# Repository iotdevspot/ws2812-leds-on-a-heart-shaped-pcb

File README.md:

# ws2812-leds-on-a-heart-shaped-pcb

### About the project
This is a WS2812 LED driver circuit with an ATTiny85 MCU. PCB and the LEDs are aligned to create a heart shape because it's a gift.  Unfortunately, I'm quite sort of time so the code is very basic and it has been created from the examples found on Adafruit's website. In the future I'll upload a newer version. This version is only capable for 4 basic effects witch can be selected with the left function button.

### Contents
* Gerber files (the version that I've sent to the fab house)
* Updated board layout and schematics
* 3D model can be found on my fusion360 gallery
* Code (Arduino sketch and hex)
* Datasheet
* Images of the result

### The following steps are required to deploy the provided .hex, or the Arduino sketch:
* Here is how to program ATTiny MCUs in Arduino IDE: [link](http://highlowtech.org/?p=1695)
* I've used external 16 MHz oscillator (AVR fuse settings needed + hex is compiled this way too) so it might be required but I assume it works on internal clock well too but code should be recompiled
* Code is based on Adafruit's [Neopixel libary and their example projects](https://learn.adafruit.com/adafruit-arduino-lesson-16-stepper-motors/breadboard-layout) so Adafruit's libary might be needed if you want to deploy it from the IDE.
* Finnaly the hex should be uploaded. You can do this by using IDE-s "Upload using programmer" option or .hex file can be uploaded throuh AVR Dude too. It's basically your choice...

### ToDo

* 3D printed mounting for the two mounting holes
* Replace the full bascic code

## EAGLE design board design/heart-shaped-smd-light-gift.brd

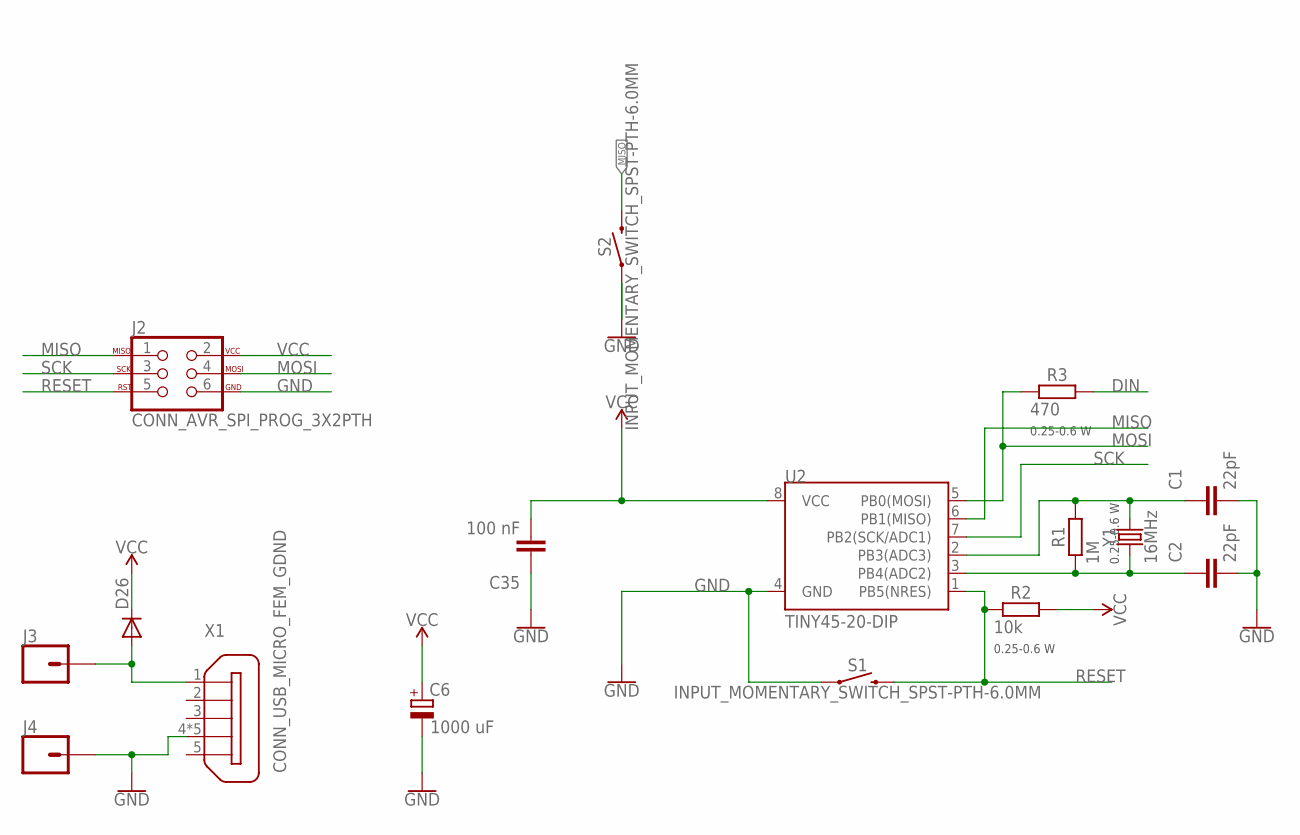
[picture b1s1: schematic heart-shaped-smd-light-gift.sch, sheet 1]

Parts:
C1, C2: 22pF; C1206I-C3216M
C6: 1000 uF; 153CLV-1010
C35: 100 nF; C1206I-C3216M
D26: DIODED-7.5; D-7.5
J2: CONN_AVR_SPI_PROG_3X2PTH; 2X3_S
J3, J4: CONN_01SNAP-MALE; SNAP-MALE
R1: 1M; 0207/7
R2: 10k; 0207/7
R3: 470; 0207/7
S1, S2: INPUT_MOMENTARY_SWITCH_SPST-PTH-6.0MM; TACTILE_SWITCH_PTH_6.0MM
U2: TINY45-20-DIP; DIP08
X1: CONN_USB_MICRO_FEM_GDND; ZX62D-B-5PA8
Y1: 16MHz; HC49US

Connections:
DIN: R3.2; also elsewhere on the board
GND: C1.2, C2.2, C6.-, C35.1, J2.6, J4.2, S1.1, S2.1, U2.4 (GND), X1.4, X1.S1 (4), X1.S2 (4), X1.S3 (4), X1.S4 (4); also elsewhere on the board
MISO: J2.1, S2.3 (2), U2.6 (PB1(MISO))
MOSI: J2.4, R3.1, U2.5 (PB0(MOSI))
unnamed: C2.1, R1.1, U2.3 (PB4(ADC2)), Y1.1
unnamed: C1.1, R1.2, U2.2 (PB3(ADC3)), Y1.2
unnamed: D26.A, J3.2, X1.1
RESET: J2.5, R2.1, S1.3 (2), U2.1 (PB5(NRES))
SCK: J2.3, U2.7 (PB2(SCK/ADC1))
VCC: C6.+, C35.2, D26.C, J2.2, R2.2, U2.8 (VCC); also elsewhere on the board

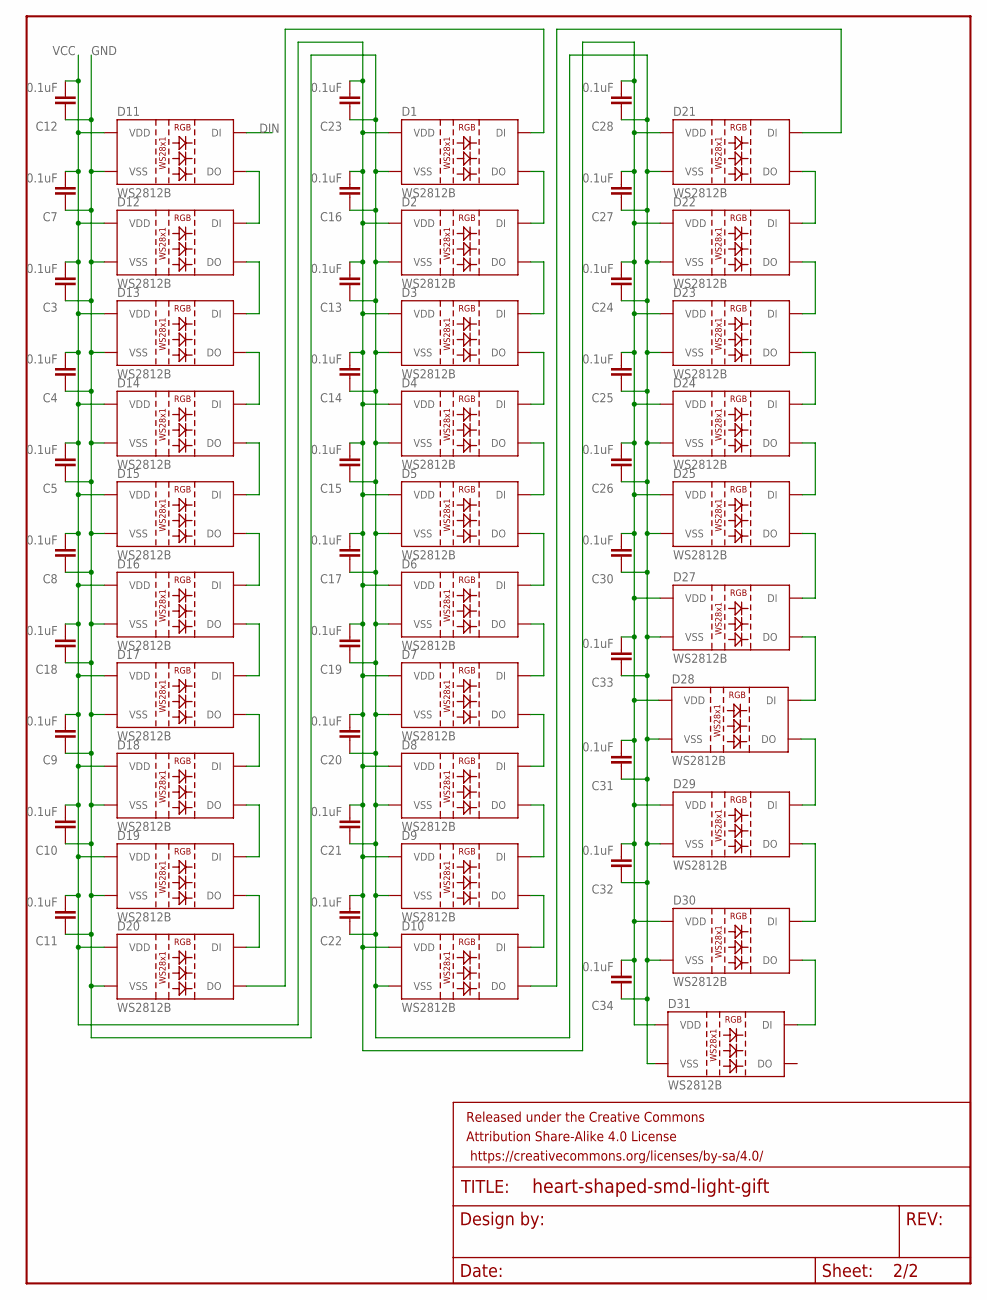
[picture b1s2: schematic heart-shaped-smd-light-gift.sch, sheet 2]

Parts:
C3, C4, C5, C7, C8, C9, C10, C11, C12, C13, C14, C15, C16, C17, C18, C19, C20, C21, C22, C23, C24, C25, C26, C27, C28, C30, C31, C32, C33, C34: 0.1uF; C1206I-C3216M
D1, D2, D3, D4, D5, D6, D7, D8, D9, D10, D11, D12, D13, D14, D15, D16, D17, D18, D19, D20, D21, D22, D23, D24, D25, D27, D28, D29, D30, D31: WS2812B
FRAME2: FRAME_LETTERNO_PACKAGE; DUMMY

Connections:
DIN: D11.4 (DI); also elsewhere on the board
DIN2: D10.2 (DO), D21.4 (DI)
GND: C3.1, C4.1, C5.1, C7.1, C8.1, C9.1, C10.1, C11.1, C12.1, C13.1, C14.1, C15.1, C16.1, C17.1, C18.1, C19.1, C20.1, C21.1, C22.1, C23.1, C24.1, C25.1, C26.1, C27.1, C28.1, C30.1, C31.1, C32.1, C33.1, C34.1, D1.3 (VSS), D2.3 (VSS), D3.3 (VSS), D4.3 (VSS), D5.3 (VSS), D6.3 (VSS), D7.3 (VSS), D8.3 (VSS), D9.3 (VSS), D10.3 (VSS), D11.3 (VSS), D12.3 (VSS), D13.3 (VSS), D14.3 (VSS), D15.3 (VSS), D16.3 (VSS), D17.3 (VSS), D18.3 (VSS), D19.3 (VSS), D20.3 (VSS), D21.3 (VSS), D22.3 (VSS), D23.3 (VSS), D24.3 (VSS), D25.3 (VSS), D27.3 (VSS), D28.3 (VSS), D29.3 (VSS), D30.3 (VSS), D31.3 (VSS); also elsewhere on the board
unnamed: D18.2 (DO), D19.4 (DI)
unnamed: D1.2 (DO), D2.4 (DI)
unnamed: D2.2 (DO), D3.4 (DI)
unnamed: D3.2 (DO), D4.4 (DI)
unnamed: D4.2 (DO), D5.4 (DI)
unnamed: D5.2 (DO), D6.4 (DI)
unnamed: D11.2 (DO), D12.4 (DI)
unnamed: D6.2 (DO), D7.4 (DI)
unnamed: D12.2 (DO), D13.4 (DI)
unnamed: D7.2 (DO), D8.4 (DI)
unnamed: D8.2 (DO), D9.4 (DI)
unnamed: D9.2 (DO), D10.4 (DI)
unnamed: D1.4 (DI), D20.2 (DO)
unnamed: D21.2 (DO), D22.4 (DI)
unnamed: D13.2 (DO), D14.4 (DI)
unnamed: D14.2 (DO), D15.4 (DI)
unnamed: D22.2 (DO), D23.4 (DI)
unnamed: D15.2 (DO), D16.4 (DI)
unnamed: D16.2 (DO), D17.4 (DI)
unnamed: D17.2 (DO), D18.4 (DI)
unnamed: D19.2 (DO), D20.4 (DI)
unnamed: D23.2 (DO), D24.4 (DI)
unnamed: D24.2 (DO), D25.4 (DI)
unnamed: D25.2 (DO), D27.4 (DI)
unnamed: D27.2 (DO), D28.4 (DI)
unnamed: D28.2 (DO), D29.4 (DI)
unnamed: D29.2 (DO), D30.4 (DI)
unnamed: D30.2 (DO), D31.4 (DI)
VCC: C3.2, C4.2, C5.2, C7.2, C8.2, C9.2, C10.2, C11.2, C12.2, C13.2, C14.2, C15.2, C16.2, C17.2, C18.2, C19.2, C20.2, C21.2, C22.2, C23.2, C24.2, C25.2, C26.2, C27.2, C28.2, C30.2, C31.2, C32.2, C33.2, C34.2, D1.1 (VDD), D2.1 (VDD), D3.1 (VDD), D4.1 (VDD), D5.1 (VDD), D6.1 (VDD), D7.1 (VDD), D8.1 (VDD), D9.1 (VDD), D10.1 (VDD), D11.1 (VDD), D12.1 (VDD), D13.1 (VDD), D14.1 (VDD), D15.1 (VDD), D16.1 (VDD), D17.1 (VDD), D18.1 (VDD), D19.1 (VDD), D20.1 (VDD), D21.1 (VDD), D22.1 (VDD), D23.1 (VDD), D24.1 (VDD), D25.1 (VDD), D27.1 (VDD), D28.1 (VDD), D29.1 (VDD), D30.1 (VDD), D31.1 (VDD); also elsewhere on the board

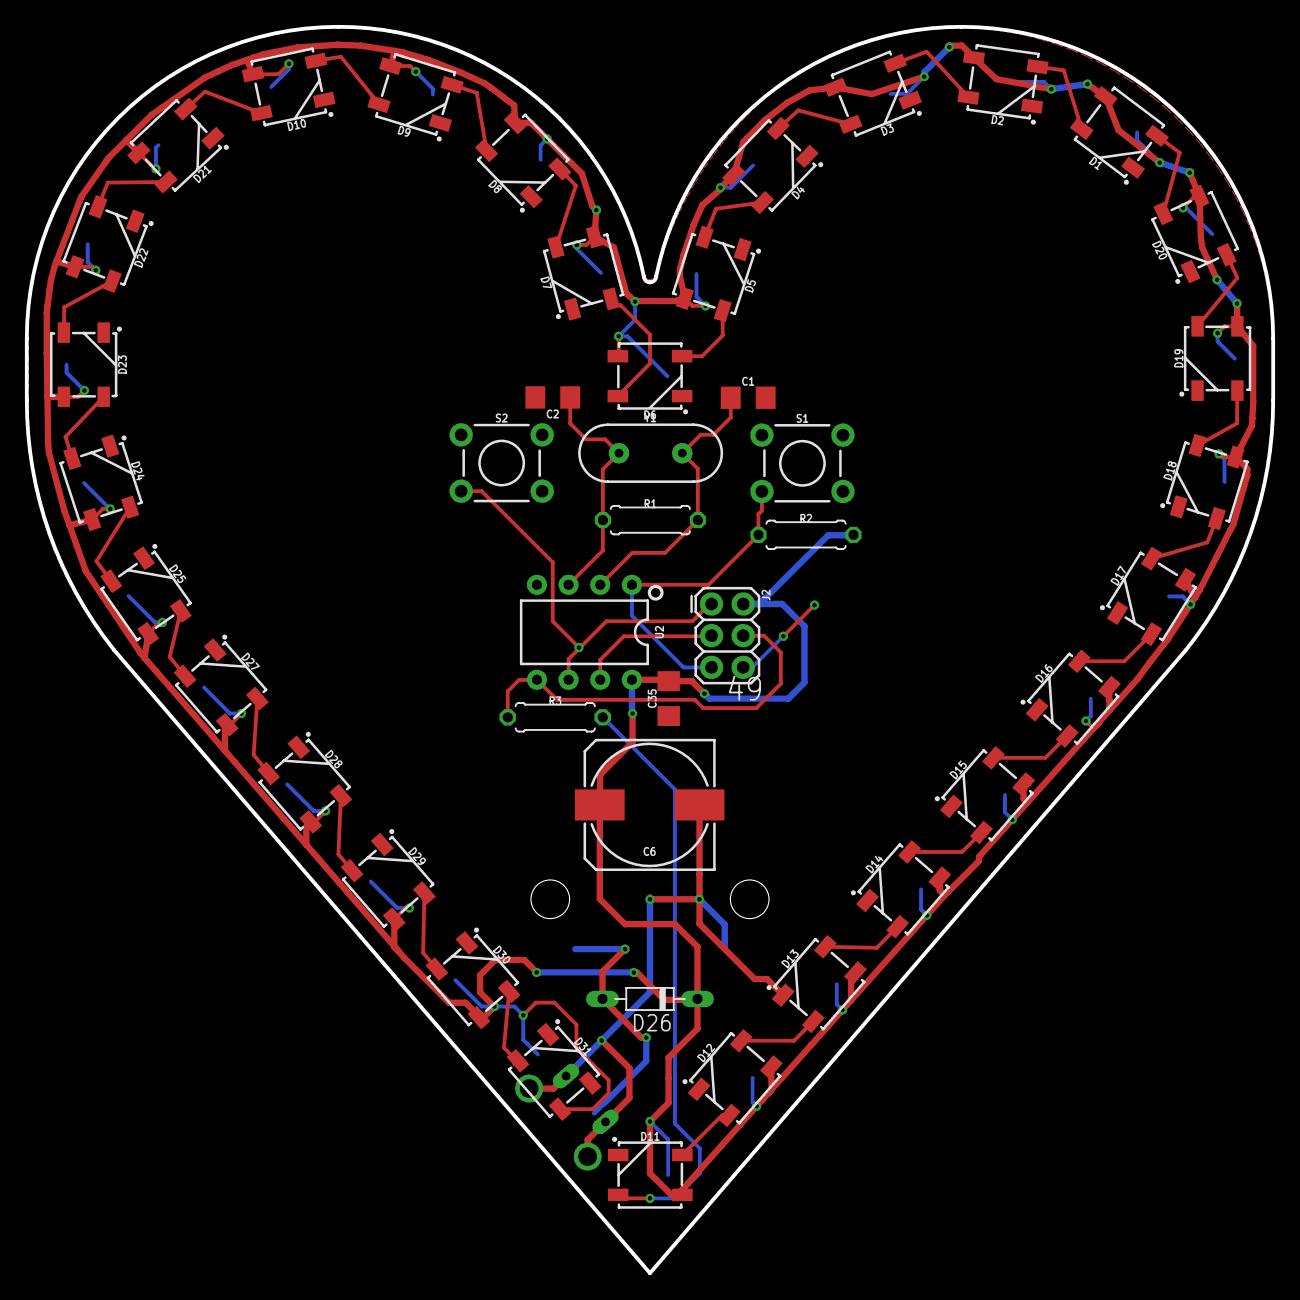
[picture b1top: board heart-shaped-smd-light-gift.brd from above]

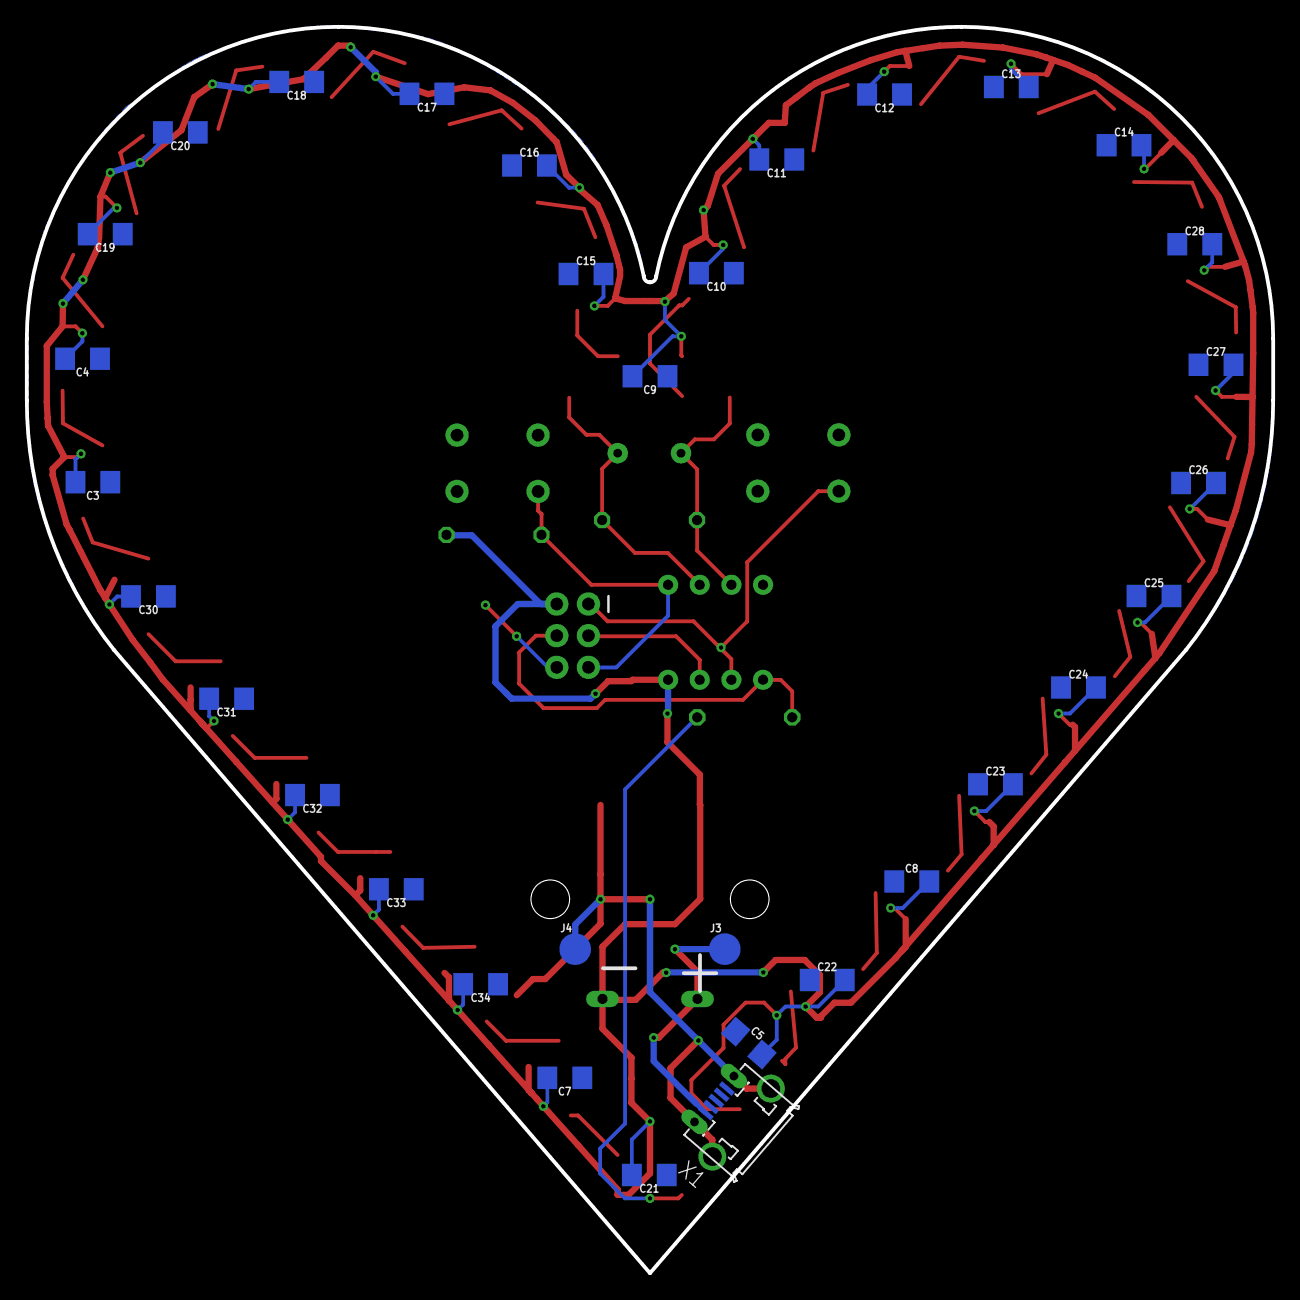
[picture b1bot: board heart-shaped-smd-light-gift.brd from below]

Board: 2 copper layers, 100.0 x 100.0 mm, 77 parts (33 on the bottom side), 39 nets.

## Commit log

2018-10-11 Compiled code for an ATTiny MCU-s with external 16 MHz oscillator
2018-10-11 New images added
2018-10-12 3D model of the PCB added
2018-12-02 Image uploaded
2018-12-02 Updated Eagle design files and gerbers

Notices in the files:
parts and their libraries:
SparkFun-PowerSymbols: Licensing: Creative Commons ShareAlike 4.0 International - https://creativecommons.org/licenses/by-sa/4.0
001-private-inventory: Released under the Creative Commons Attribution Share-Alike 4.0 License
001-private-inventory: https://creativecommons.org/licenses/by-sa/4.0
